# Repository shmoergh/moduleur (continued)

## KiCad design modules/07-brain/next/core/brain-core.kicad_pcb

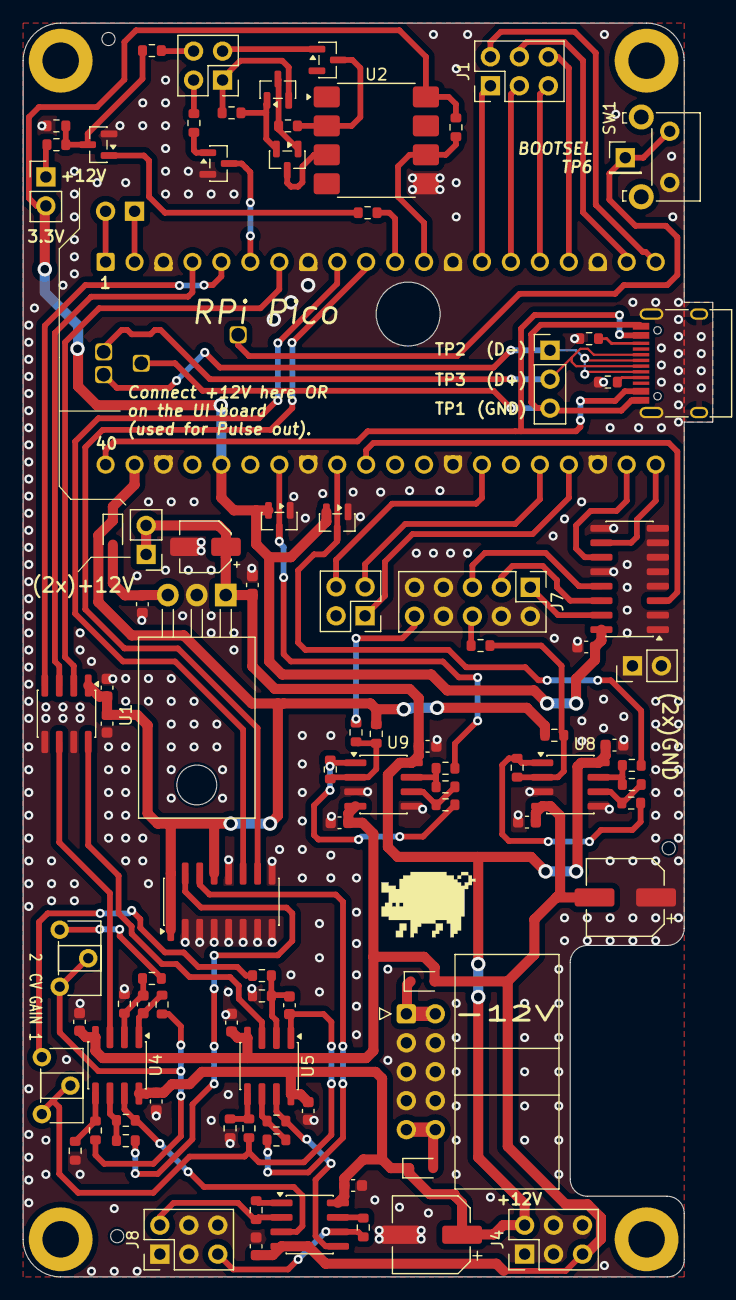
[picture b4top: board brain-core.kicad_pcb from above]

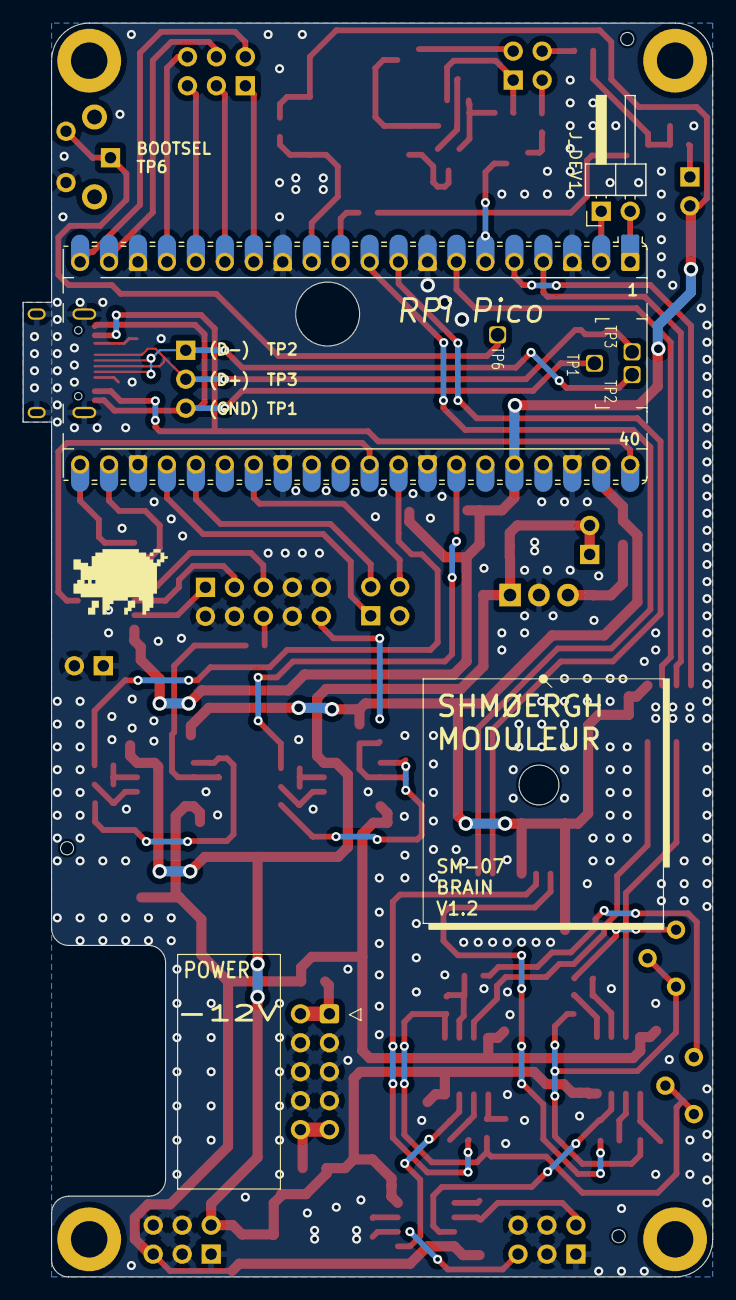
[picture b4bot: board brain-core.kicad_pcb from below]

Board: 2 copper layers, 60.5 x 110.0 mm, 99 parts (2 on the bottom side), 84 nets.

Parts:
C1: 10u; CP_Elec_4x5.4
C2: 330n; C_0603_1608Metric_Pad1.08x0.95mm_HandSolder
C3, C6, C7, C8, C9, C12, C13, C14, C15, C16, C17, C19, C20: 100n; C_0603_1608Metric
C4, C5: 100u; CP_Elec_6.3x7.7
C10, C11: 22p; C_0603_1608Metric
C18: 10u; C_0603_1608Metric
D1, D2, D3: 1N5817; D_SOD-323
D4: BAT54; SOT-23
D5, D6: BAT54S; SOT-23
H1, H2, H3, H4: MountingHole; MountingHole_3.2mm_M3_DIN965_Pad
J1, J4, J8: Conn_02x03_Odd_Even; PinHeader_2x03_P2.54mm_Vertical
J2, J3: Conn_02x02_Odd_Even; PinHeader_2x02_P2.54mm_Vertical
J5, J9, J10: Conn_01x02; PinHeader_1x02_P2.54mm_Vertical
J6: Conn_02x05_Odd_Even; IDC-Header_2x05_P2.54mm_Horizontal
J7: Conn_02x05_Odd_Even; PinHeader_2x05_P2.54mm_Vertical
J11: Conn_01x01; PinHeader_1x01_P2.54mm_Vertical
J13: Conn_01x03; PinHeader_1x03_P2.54mm_Vertical
J_DEV1: Conn_01x02; PinHeader_1x02_P2.54mm_Horizontal
J_USB_C_EXTENSION1: USB_C_Receptacle_USB2.0_16P; USB_C_Receptacle_HRO_TYPE-C-31-M-12
Q1, Q3, Q6, Q7: MMBT3904; SOT-23
R1, R14, R15, R16, R17, R18, R19, R20, R21, R24, R26, R30, R31, R32, R33: 100k; R_0603_1608Metric
R2, R7: 3.3k; R_0603_1608Metric
R3: 10k; R_0603_1608Metric
R4: 7.5k; R_0603_1608Metric
R5: 2.2k; R_0603_1608Metric
R6: 120; R_0603_1608Metric
R8, R9: 47k; R_0603_1608Metric
R10, R11: 62k; R_0603_1608Metric
R12, R13, R22, R23, R34, R35: 1k; R_0603_1608Metric
R25, R27: 120k; R_0603_1608Metric
R28, R29: 33k; R_0603_1608Metric
R36, R37: 5.1k; R_0603_1608Metric
RV_CV_GAIN1, RV_CV_GAIN2: 10k; Potentiometer_ACP_CA6-H2,5_Horizontal
SW1: SW_SPST; SW_Tactile_SKHH_Angled
U1: LM7805_TO220; TO-220-3_Horizontal_TabDown
U2: 6N137; SOP-8_6.605x9.655mm_P2.54mm
U3: Pico; RaspberryPi_Pico_Common_Unspecified
U4, U5, U8, U9, U11: TL072; SOIC-8_3.9x4.9mm_P1.27mm
U6: MCP4822; SOIC-8_3.9x4.9mm_P1.27mm
U7: 74HC4053B; SOIC-16_3.9x9.9mm_P1.27mm
U10: 74HC4051; SOIC-16_3.9x9.9mm_P1.27mm

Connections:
+3.3V: C16.1, D5.2 (K), D6.2 (K), J10.2, R7.2, U2.8 (VCC), U3.36 (3V3), U10.16 (VCC)
+5V: C17.1, C18.1, D1.1 (K), R24.1, R26.1, U3.39 (VSYS), U6.1 (Vdd), U7.1 (B1), U7.13 (A1), U7.16 (VDD)
+12V: C1.1, C2.1, C4.1, C6.1, C8.1, C12.1, C14.1, C19.1, D2.1 (K), J4.2, J9.1, J9.2, J10.1, R3.2, U1.1 (VI), U4.8 (V+), U5.8 (V+), U8.8 (V+), U9.8 (V+), U11.8 (V+)
-12V: C5.2, C7.2, C9.2, C13.2, C15.2, C20.2, D3.2 (A), J4.5, U4.4 (V-), U5.4 (V-), U8.4 (V-), U9.4 (V-), U11.4 (V-)
/GPIO_2: U3.4 (GPIO2), U6.3 (SCK)
/GPIO_3: U3.5 (GPIO3), U6.4 (SDI)
/GPIO_4: Q1.3 (C), U3.6 (GPIO4)
/GPIO_5: U3.7 (GPIO5), U6.2 (~CS)
/GPIO_6: U3.9 (GPIO6), U7.11 (S1)
/GPIO_7: U3.10 (GPIO7), U7.10 (S2)
/GPIO_8: R2.1, U3.11 (GPIO8)
/GPIO_9: R7.1, U2.6 (VO), U3.12 (GPIO9)
/GPIO_16: U3.22 (GPIO17), U10.11 (S0)
/GPIO_17: U3.21 (GPIO16), U10.10 (S1)
/GPIO_26: U3.31 (GPIO26_ADC0), U10.3 (A)
/GPIO_27: D5.3 (COM), R34.2, U3.32 (GPIO27_ADC1)
/GPIO_28: D6.3 (COM), R35.2, U3.34 (GPIO28_ADC2)
/MCU/TP1: J13.3, J_USB_C_EXTENSION1.A1 (GND), J_USB_C_EXTENSION1.A12 (GND), J_USB_C_EXTENSION1.B1 (GND), J_USB_C_EXTENSION1.B12 (GND), U3.44 (TP1)
/MCU/TP2: J13.1, J_USB_C_EXTENSION1.A7 (D-), J_USB_C_EXTENSION1.B7 (D-), U3.45 (TP2)
/MCU/TP3: J13.2, J_USB_C_EXTENSION1.A6 (D+), J_USB_C_EXTENSION1.B6 (D+), U3.46 (TP3)
/MCU/TP6: J11.1, SW1.1 (A), U3.47 (TP6)
/MCU/UART_RX: J_DEV1.1, U3.2 (GPIO1)
/MCU/UART_TX: J_DEV1.2, U3.1 (GPIO0)
AUDIO_CV_IN_1: J7.6, R25.1
AUDIO_CV_IN_2: J7.10, R27.1
AUDIO_CV_OUT_1: J8.5, R23.2, U11.6 (-)
AUDIO_CV_OUT_2: J8.2, R22.2, U11.2 (-)
BTN_1: J3.1, U3.24 (GPIO18)
BTN_2: J3.3, U3.25 (GPIO19)
BTN_LED_1: J3.4, U3.27 (GPIO21)
GND: C1.2, C2.2, C3.2, C4.2, C5.1, C6.2, C7.1, C8.2, C9.1, C12.2, C13.1, C14.2, C15.1, C16.2, C17.2, C18.2, C19.2, C20.1, D5.1 (A), D6.1 (A), J4.1, J4.3, J4.4, J4.6, J5.1, J5.2, J6.3, J6.4, J6.5, J6.6, J6.7, J6.8, J7.2, J7.4, J7.7, J7.8, J7.9, J8.1, J8.3, J8.4, J8.6, J_USB_C_EXTENSION1.S1 (SHIELD), Q1.2 (E), Q3.2 (E), R4.1, R8.1, R9.1, R16.1, R17.1, R36.2, R37.2, SW1.2 (B), U1.2 (GND), U2.5 (GND), U3.3 (GND), U3.8 (GND), U3.13 (GND), U3.18 (GND), U3.23 (GND), U3.28 (GND), U3.33 (AGND), U3.38 (GND), U6.5 (~LDAC), U6.7 (Vss), U7.2 (B0), U7.3 (C1), U7.4 (C), U7.5 (C0), U7.6 (INH), U7.7 (VEE), U7.8 (VSS), U7.9 (S3), U7.12 (A0), U8.3 (+), U8.5 (+), U9.3 (+), U9.5 (+), U10.1 (A4), U10.2 (A6), U10.4 (A7), U10.5 (A5), U10.6 (~E), U10.7 (VEE), U10.8 (GND), U10.9 (S2), U10.12 (A3)
LED_1: J1.1, U3.14 (GPIO10)
LED_2: J1.3, U3.15 (GPIO11)
LED_3: J1.5, U3.16 (GPIO12)
LED_4: J1.6, U3.17 (GPIO13)
LED_5: J1.4, U3.19 (GPIO14)
LED_6: J1.2, U3.20 (GPIO15)
MIDI_4R: D4.1 (A), J2.3
MIDI_5T: J2.1, Q6.2 (E), R6.1
unnamed: C10.2, R12.1, U4.1
unnamed: C11.2, R15.1, RV_CV_GAIN1.2, RV_CV_GAIN1.3, U5.1
unnamed: C3.1, D1.2 (A), U1.3 (VO)
unnamed: D2.2 (A), J6.9, J6.10
unnamed: D3.1 (K), J6.1, J6.2
unnamed: D4.3 (K), R5.2, U2.2 (A)
unnamed: J_USB_C_EXTENSION1.A5 (CC1), R36.1
unnamed: J_USB_C_EXTENSION1.B5 (CC2), R37.1
unnamed: Q1.1 (B), R1.2
unnamed: Q3.1 (B), R2.2
unnamed: Q3.3 (C), R3.1, R4.2, R13.1
unnamed: Q6.1 (B), Q7.2 (E), R6.2
unnamed: Q6.3 (C), Q7.1 (B), R5.1
unnamed: Q7.3 (C), U2.3 (C)
unnamed: R10.2, RV_CV_GAIN2.1
unnamed: R11.2, RV_CV_GAIN1.1
unnamed: R12.2, R14.1, RV_CV_GAIN2.2, RV_CV_GAIN2.3
unnamed: R22.1, U11.1
unnamed: R23.1, U11.7
unnamed: R28.2, R30.1, U8.1
unnamed: R29.2, R31.1, U9.1
unnamed: R32.2, R34.1, U8.7
unnamed: R33.2, R35.1, U9.7
unnamed: J_USB_C_EXTENSION1.A4 (VBUS), J_USB_C_EXTENSION1.A9 (VBUS), J_USB_C_EXTENSION1.B4 (VBUS), J_USB_C_EXTENSION1.B9 (VBUS), U3.40 (VBUS)
unnamed: U4.3 (+), U6.6 (VB)
unnamed: C10.1, R8.2, R10.1, U4.2 (-)
unnamed: R14.2, R16.2, U4.5 (+)
unnamed: R19.1, R20.1, U4.6 (-)
unnamed: U5.3 (+), U6.8 (VA)
unnamed: C11.1, R9.2, R11.1, U5.2 (-)
unnamed: R15.2, R17.2, U5.5 (+)
unnamed: R18.2, R21.1, U5.6 (-)
unnamed: R18.1, U7.14 (A)
unnamed: R19.2, U7.15 (B)
unnamed: R24.2, R25.2, R28.1, U8.2 (-)
unnamed: R30.2, R32.1, U8.6 (-)
unnamed: R26.2, R27.2, R29.1, U9.2 (-)
unnamed: R31.2, R33.1, U9.6 (-)
unnamed: R20.2, U4.7, U11.3 (+)
unnamed: R21.2, U5.7, U11.5 (+)
POT_1: J7.5, U10.13 (A0)
POT_2: J7.3, U10.14 (A1)
POT_3: J7.1, U10.15 (A2)
PULSE_IN: J2.2, R1.1
PULSE_OUT: J2.4, R13.2

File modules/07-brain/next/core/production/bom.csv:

Designator,Footprint,Quantity,Value,LCSC Part #
C1,CP_Elec_4x5.4,1,10u,C46550410
"C10, C11",0603,2,22p,C1653
"C12, C13, C14, C15, C16, C17, C19, C20, C3, C6, C7, C8, C9",0603,13,100n,C14663
C18,0603,1,10u,C19702
C2,0603,1,330n,C188679
"C4, C5",CP_Elec_6.3x7.7,2,100u,C2836442
"D1, D2, D3",D_SOD-323,3,1N5817,C5190152
D4,SOT-23,1,BAT54,C22466368
"D5, D6",SOT-23,2,BAT54S,C7420333
"J1, J4, J8",PinHeader_2x03_P2.54mm_Vertical,3,Conn_02x03_Odd_Even,
"J10, J5, J9",PinHeader_1x02_P2.54mm_Vertical,3,Conn_01x02,
J11,PinHeader_1x01_P2.54mm_Vertical,1,Conn_01x01,
J13,PinHeader_1x03_P2.54mm_Vertical,1,Conn_01x03,
"J2, J3",PinHeader_2x02_P2.54mm_Vertical,2,Conn_02x02_Odd_Even,
J6,IDC-Header_2x05_P2.54mm_Horizontal,1,Conn_02x05_Odd_Even,
J7,PinHeader_2x05_P2.54mm_Vertical,1,Conn_02x05_Odd_Even,
J_DEV1,PinHeader_1x02_P2.54mm_Horizontal,1,Conn_01x02,
J_USB_C_EXTENSION1,USB_C_Receptacle_HRO_TYPE-C-31-M-12,1,USB_C_Receptacle_USB2.0_16P,C165948
"Q1, Q3, Q6, Q7",SOT-23,4,MMBT3904,C20526
"R1, R14, R15, R16, R17, R18, R19, R20, R21, R24, R26, R30, R31, R32, R33",0603,15,100k,C25803
"R10, R11",0603,2,62k,C23221
"R12, R13, R22, R23, R34, R35",0603,6,1k,C21190
"R2, R7",0603,2,3.3k,C22978
"R25, R27",0603,2,120k,C25808
"R28, R29",0603,2,33k,C4216
R3,0603,1,10k,C25804
"R36, R37",0603,2,5.1k,C23186
R4,0603,1,7.5k,C23234
R5,0603,1,2.2k,C4190
R6,0603,1,120,C22787
"R8, R9",0603,2,47k,C25819
"RV_CV_GAIN1, RV_CV_GAIN2","Potentiometer_ACP_CA6-H2,5_Horizontal",2,10k,
SW1,SW_Tactile_SKHH_Angled,1,SW_SPST,
U1,TO-220-3_Horizontal_TabDown,1,LM7805_TO220,
U10,SOIC-16_3.9x9.9mm_P1.27mm,1,74HC4051,C9386
"U11, U4, U5, U8, U9",SOIC-8_3.9x4.9mm_P1.27mm,5,TL072,C6961
U2,SOP-8_6.605x9.655mm_P2.54mm,1,6N137,C92651
U3,RaspberryPi_Pico_Common_Unspecified,1,Pico,
U6,SOIC-8_3.9x4.9mm_P1.27mm,1,MCP4822,C623653
U7,SOIC-16_3.9x9.9mm_P1.27mm,1,74HC4053B,C5647

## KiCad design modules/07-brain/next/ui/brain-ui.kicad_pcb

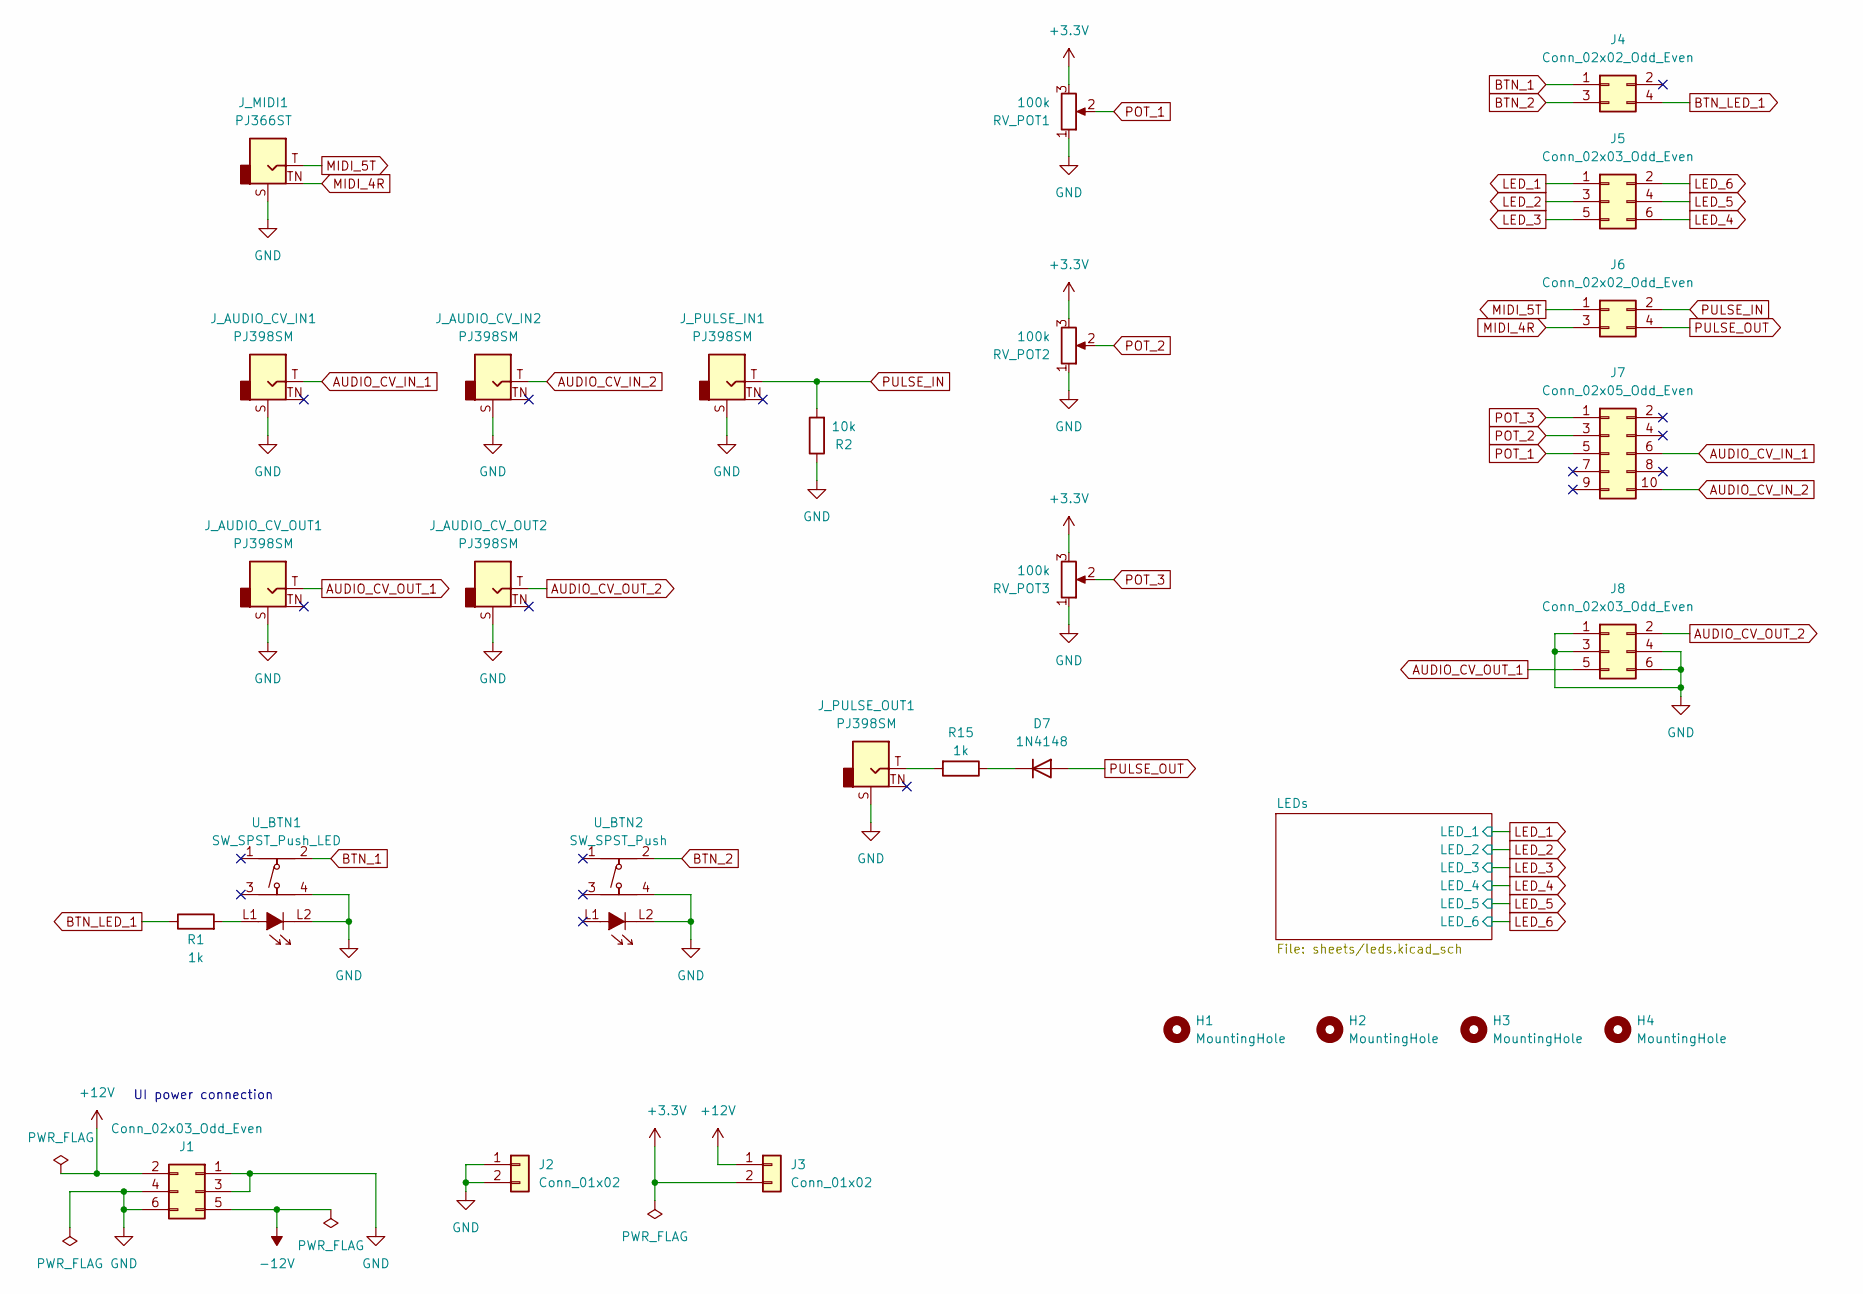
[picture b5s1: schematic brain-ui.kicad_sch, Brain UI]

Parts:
D7: 1N4148; D_DO-35_SOD27_P7.62mm_Horizontal
H1, H2, H3, H4: MountingHole; MountingHole_3.2mm_M3_DIN965_Pad
J1, J5, J8: Conn_02x03_Odd_Even; PinSocket_2x03_P2.54mm_Vertical; Part no. 200-SSW10301TD
J2, J3: Conn_01x02; PinSocket_1x02_P2.54mm_Vertical; Part no. 200-SSW10201TS
J4, J6: Conn_02x02_Odd_Even; PinSocket_2x02_P2.54mm_Vertical; Part no. 200-SSW10206TD
J7: Conn_02x05_Odd_Even; PinSocket_2x05_P2.54mm_Vertical; Part no. 200-SSW10501TD
J_AUDIO_CV_IN1, J_AUDIO_CV_IN2: PJ398SM; Jack_3.5mm_QingPu_WQP-PJ398SM_Vertical_CircularHoles; Part no. PJ398SM
J_AUDIO_CV_OUT1, J_AUDIO_CV_OUT2: PJ398SM; Jack_3.5mm_QingPu_WQP-PJ398SM_Vertical_CircularHoles; Part no. PJ398SM
J_MIDI1: PJ366ST; Jack_3.5mm_QingPu_WQP-PJ398SM_Vertical_CircularHoles; Part no. PJ366ST Stereo
J_PULSE_IN1: PJ398SM; Jack_3.5mm_QingPu_WQP-PJ398SM_Vertical_CircularHoles; Part no. PJ398SM
J_PULSE_OUT1: PJ398SM; Jack_3.5mm_QingPu_WQP-PJ398SM_Vertical_CircularHoles; Part no. PJ398SM
R1: 1k; R_Axial_DIN0207_L6.3mm_D2.5mm_P7.62mm_Horizontal; Part no. 603-MFR-25FRE52-1K
R2: 10k; R_Axial_DIN0207_L6.3mm_D2.5mm_P7.62mm_Horizontal; Part no. 603-MFR25SFTF52-10K
R15: 1k; R_Axial_DIN0207_L6.3mm_D2.5mm_P7.62mm_Horizontal; Part no. 603-MFR25SFTF52-10K
RV_POT1, RV_POT2, RV_POT3: 100k; Potentiometer_Bourns_Single-PTV09A; Part no. 652-PTV09A4025UB104
U_BTN1: SW_SPST_Push_LED; SPST_Circular_Pushbutton_LED; Part no. 611-D6RLRDF1LFS
U_BTN2: SW_SPST_Push; SPST_Circular_Pushbutton_LED; Part no. 611-D6R90F2LFS

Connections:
+3.3V: J3.2, RV_POT1.3, RV_POT2.3, RV_POT3.3
+12V: J1.2, J3.1; also elsewhere on the board
-12V: J1.5
AUDIO_CV_IN_1: J7.6, J_AUDIO_CV_IN1.T
AUDIO_CV_IN_2: J7.10, J_AUDIO_CV_IN2.T
AUDIO_CV_OUT_1: J8.5, J_AUDIO_CV_OUT1.T
AUDIO_CV_OUT_2: J8.2, J_AUDIO_CV_OUT2.T
BTN_1: J4.1, U_BTN1.2
BTN_2: J4.3, U_BTN2.2
BTN_LED_1: J4.4, R1.1
GND: H3.1, J1.1, J1.3, J1.4, J1.6, J2.1, J2.2, J8.1, J8.3, J8.4, J8.6, J_AUDIO_CV_IN1.S, J_AUDIO_CV_IN2.S, J_AUDIO_CV_OUT1.S, J_AUDIO_CV_OUT2.S, J_MIDI1.S, J_PULSE_IN1.S, J_PULSE_OUT1.S, R2.1, RV_POT1.1, RV_POT2.1, RV_POT3.1, U_BTN1.4, U_BTN1.L2, U_BTN2.4, U_BTN2.L2; also elsewhere on the board
LED_1: J5.1; also elsewhere on the board
LED_2: J5.3; also elsewhere on the board
LED_3: J5.5; also elsewhere on the board
LED_4: J5.6; also elsewhere on the board
LED_5: J5.4; also elsewhere on the board
LED_6: J5.2; also elsewhere on the board
MIDI_4R: J6.3, J_MIDI1.TN
MIDI_5T: J6.1, J_MIDI1.T
unnamed: D7.1 (K), R15.1
unnamed: J_PULSE_OUT1.T, R15.2
unnamed: R1.2, U_BTN1.L1
POT_1: J7.5, RV_POT1.2
POT_2: J7.3, RV_POT2.2
POT_3: J7.1, RV_POT3.2
PULSE_IN: J6.2, J_PULSE_IN1.T, R2.2
PULSE_OUT: D7.2 (A), J6.4

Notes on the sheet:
UI power connection

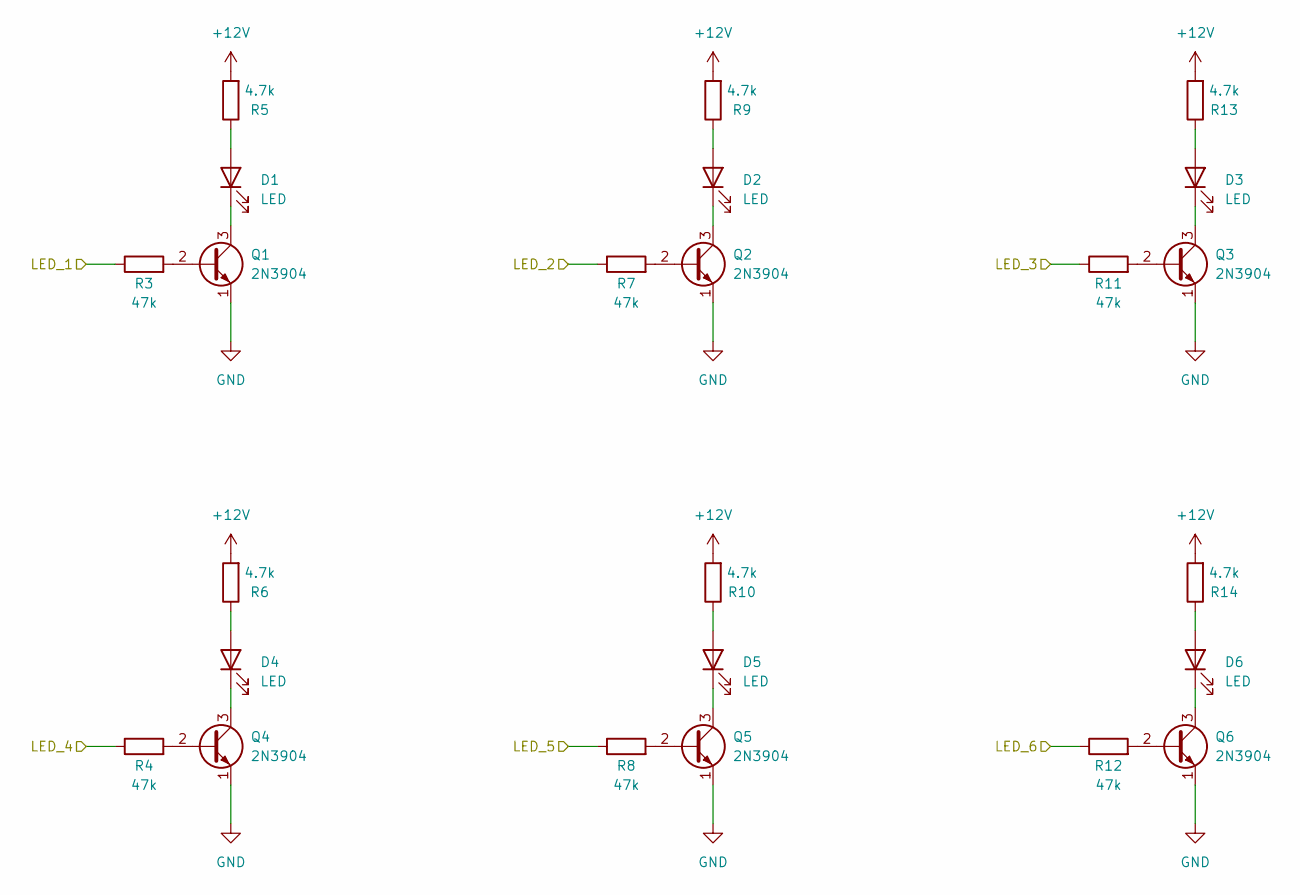
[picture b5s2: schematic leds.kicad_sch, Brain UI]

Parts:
D1, D2, D3, D4, D5, D6: LED; LED_D3.0mm
Q1, Q2, Q3, Q4, Q5, Q6: 2N3904; TO-92_Inline_Wide; Part no. 637-2N3904
R3, R4, R7, R8, R11, R12: 47k; R_Axial_DIN0207_L6.3mm_D2.5mm_P7.62mm_Horizontal; Part no. 603-MFR-25FRF52-47K; LCSC C25803
R5, R6, R9, R10, R13, R14: 4.7k; R_Axial_DIN0207_L6.3mm_D2.5mm_P7.62mm_Horizontal; Part no. 603-MFR25SFTF52-4K7

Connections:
+12V: R5.2, R6.2, R9.2, R10.2, R13.2, R14.2; also elsewhere on the board
GND: Q1.1 (E), Q2.1 (E), Q3.1 (E), Q4.1 (E), Q5.1 (E), Q6.1 (E); also elsewhere on the board
LED_1: R3.1; also elsewhere on the board
LED_2: R7.1; also elsewhere on the board
LED_3: R11.1; also elsewhere on the board
LED_4: R4.1; also elsewhere on the board
LED_5: R8.1; also elsewhere on the board
LED_6: R12.1; also elsewhere on the board
unnamed: D1.2 (A), R5.1
unnamed: D1.1 (K), Q1.3 (C)
unnamed: D2.2 (A), R9.1
unnamed: D2.1 (K), Q2.3 (C)
unnamed: D3.2 (A), R13.1
unnamed: D3.1 (K), Q3.3 (C)
unnamed: D4.2 (A), R6.1
unnamed: D4.1 (K), Q4.3 (C)
unnamed: D5.2 (A), R10.1
unnamed: D5.1 (K), Q5.3 (C)
unnamed: D6.2 (A), R14.1
unnamed: D6.1 (K), Q6.3 (C)
unnamed: Q1.2 (B), R3.2
unnamed: Q2.2 (B), R7.2
unnamed: Q3.2 (B), R11.2
unnamed: Q4.2 (B), R4.2
unnamed: Q5.2 (B), R8.2
unnamed: Q6.2 (B), R12.2

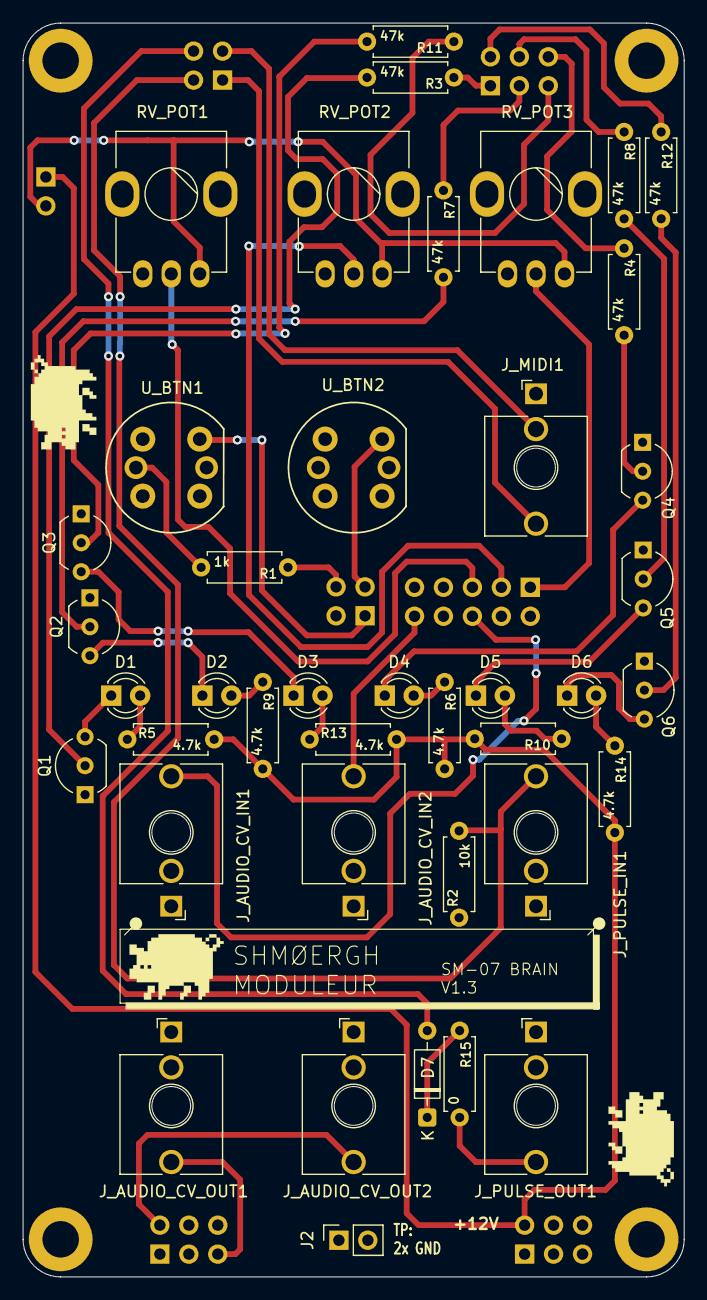
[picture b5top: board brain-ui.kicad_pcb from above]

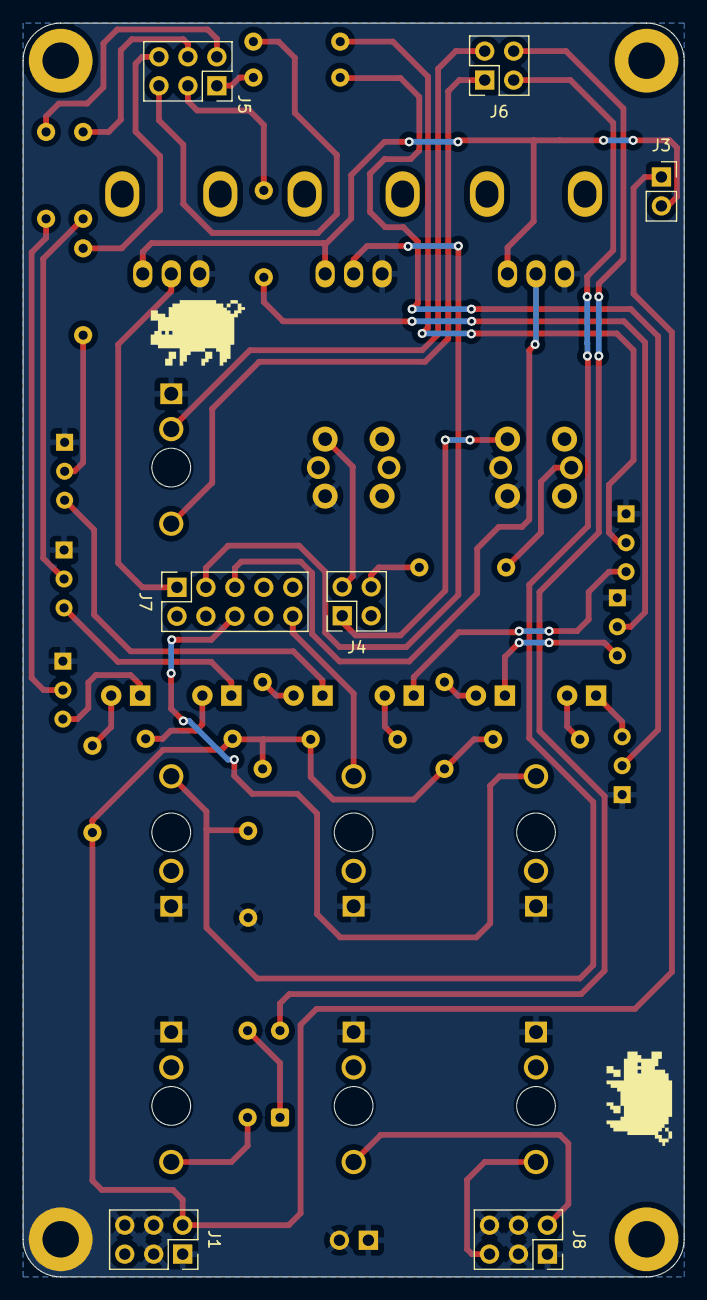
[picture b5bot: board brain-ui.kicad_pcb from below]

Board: 2 copper layers, 58.0 x 110.0 mm, 52 parts (7 on the bottom side), 44 nets.

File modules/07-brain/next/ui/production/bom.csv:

Designator,Footprint,Quantity,Value,LCSC Part #
"D1, D2, D3, D4, D5, D6",LED_D3.0mm,6,LED,
D7,D_DO-35_SOD27_P7.62mm_Horizontal,1,1N4148,
"J1, J5, J8",PinSocket_2x03_P2.54mm_Vertical,3,Conn_02x03_Odd_Even,
"J2, J3",PinSocket_1x02_P2.54mm_Vertical,2,Conn_01x02,
"J4, J6",PinSocket_2x02_P2.54mm_Vertical,2,Conn_02x02_Odd_Even,
J7,PinSocket_2x05_P2.54mm_Vertical,1,Conn_02x05_Odd_Even,
"J_AUDIO_CV_IN1, J_AUDIO_CV_IN2, J_AUDIO_CV_OUT1, J_AUDIO_CV_OUT2, J_PULSE_IN1, J_PULSE_OUT1",Jack_3.5mm_QingPu_WQP-PJ398SM_Vertical_CircularHoles,6,PJ398SM,
J_MIDI1,Jack_3.5mm_QingPu_WQP-PJ398SM_Vertical_CircularHoles,1,PJ366ST,
"Q1, Q2, Q3, Q4, Q5, Q6",TO-92_Inline_Wide,6,2N3904,
"R1, R15",R_Axial_DIN0207_L6.3mm_D2.5mm_P7.62mm_Horizontal,2,1k,
"R10, R13, R14, R5, R6, R9",R_Axial_DIN0207_L6.3mm_D2.5mm_P7.62mm_Horizontal,6,4.7k,
"R11, R12, R3, R4, R7, R8",R_Axial_DIN0207_L6.3mm_D2.5mm_P7.62mm_Horizontal,6,47k,C25803
R2,R_Axial_DIN0207_L6.3mm_D2.5mm_P7.62mm_Horizontal,1,10k,
"RV_POT1, RV_POT2, RV_POT3",Potentiometer_Bourns_Single-PTV09A,3,100k,
U_BTN1,SPST_Circular_Pushbutton_LED,1,SW_SPST_Push_LED,
U_BTN2,SPST_Circular_Pushbutton_LED,1,SW_SPST_Push,

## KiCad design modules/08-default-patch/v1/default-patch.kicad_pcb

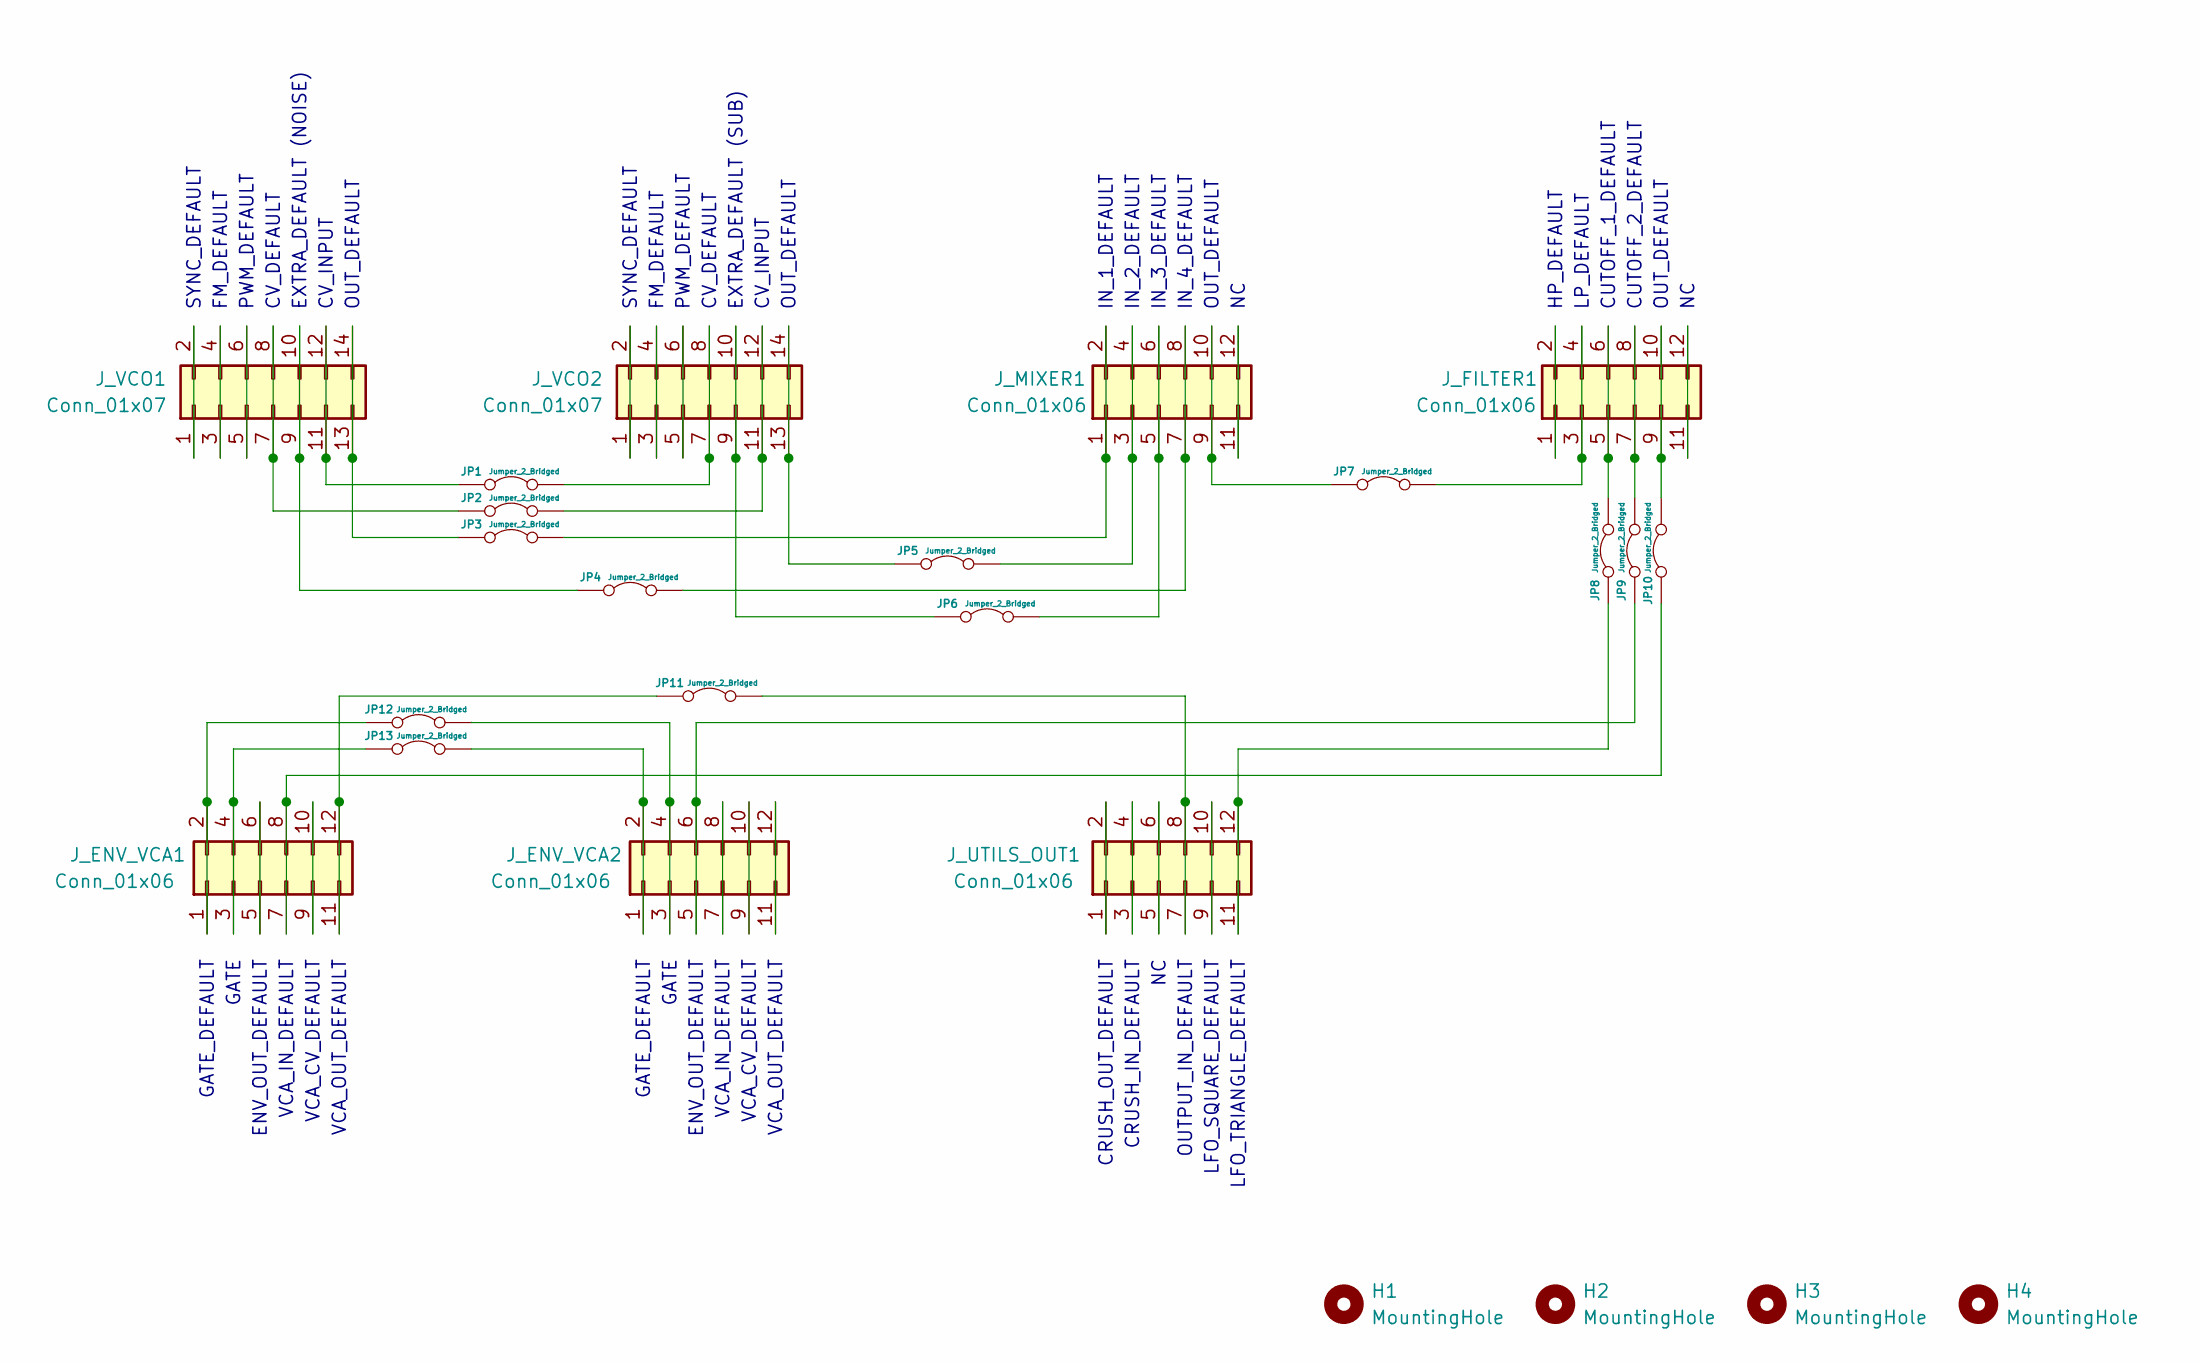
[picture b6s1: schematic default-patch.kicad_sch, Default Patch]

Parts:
H1, H2, H3, H4: MountingHole; MountingHole_3.2mm_M3
JP1, JP2, JP3, JP4, JP5, JP6, JP7, JP8, JP9, JP10, JP11, JP12, JP13: Jumper_2_Bridged; SolderJumper-2_P1.3mm_Bridged_RoundedPad1.0x1.5mm
J_ENV_VCA1, J_ENV_VCA2: Conn_01x06; PinHeader_2x06_P2.54mm_Vertical; Part No. 200-MTSW12009TS500
J_FILTER1: Conn_01x06; PinHeader_2x06_P2.54mm_Vertical; Part No. 200-MTSW12009TS500
J_MIXER1: Conn_01x06; PinHeader_2x06_P2.54mm_Vertical; Part No. 200-MTSW12009TS500
J_UTILS_OUT1: Conn_01x06; PinHeader_2x06_P2.54mm_Vertical; Part No. 200-MTSW12009TS500
J_VCO1, J_VCO2: Conn_01x07; PinHeader_2x07_P2.54mm_Vertical; Part No. 200-MTSW12009TS500

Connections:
unnamed: JP1.1 (A), J_VCO1.11, J_VCO1.12
unnamed: JP1.2 (B), J_VCO2.7, J_VCO2.8
unnamed: JP2.1 (A), J_VCO1.7, J_VCO1.8
unnamed: JP2.2 (B), J_VCO2.11, J_VCO2.12
unnamed: JP3.1 (A), J_VCO1.13, J_VCO1.14
unnamed: JP3.2 (B), J_MIXER1.1, J_MIXER1.2
unnamed: JP4.1 (A), J_VCO1.9, J_VCO1.10
unnamed: JP4.2 (B), J_MIXER1.7, J_MIXER1.8
unnamed: JP5.1 (A), J_VCO2.13, J_VCO2.14
unnamed: JP5.2 (B), J_MIXER1.3, J_MIXER1.4
unnamed: JP6.1 (A), J_VCO2.9, J_VCO2.10
unnamed: JP6.2 (B), J_MIXER1.5, J_MIXER1.6
unnamed: JP7.1 (A), J_MIXER1.9, J_MIXER1.10
unnamed: JP7.2 (B), J_FILTER1.3, J_FILTER1.4
unnamed: JP8.1 (A), J_UTILS_OUT1.11, J_UTILS_OUT1.12
unnamed: JP8.2 (B), J_FILTER1.5, J_FILTER1.6
unnamed: JP9.1 (A), J_ENV_VCA2.5, J_ENV_VCA2.6
unnamed: JP9.2 (B), J_FILTER1.7, J_FILTER1.8
unnamed: JP10.1 (A), J_ENV_VCA1.7, J_ENV_VCA1.8
unnamed: JP10.2 (B), J_FILTER1.9, J_FILTER1.10
unnamed: JP11.1 (A), J_ENV_VCA1.11, J_ENV_VCA1.12
unnamed: JP11.2 (B), J_UTILS_OUT1.7, J_UTILS_OUT1.8
unnamed: JP12.1 (A), J_ENV_VCA1.1, J_ENV_VCA1.2
unnamed: JP12.2 (B), J_ENV_VCA2.3, J_ENV_VCA2.4
unnamed: JP13.1 (A), J_ENV_VCA1.3, J_ENV_VCA1.4
unnamed: JP13.2 (B), J_ENV_VCA2.1, J_ENV_VCA2.2
unnamed: J_ENV_VCA1.5, J_ENV_VCA1.6
unnamed: J_ENV_VCA1.9, J_ENV_VCA1.10
unnamed: J_ENV_VCA2.7, J_ENV_VCA2.8
unnamed: J_ENV_VCA2.9, J_ENV_VCA2.10
unnamed: J_ENV_VCA2.11, J_ENV_VCA2.12
unnamed: J_FILTER1.1, J_FILTER1.2
unnamed: J_FILTER1.11, J_FILTER1.12
unnamed: J_MIXER1.11, J_MIXER1.12
unnamed: J_UTILS_OUT1.1, J_UTILS_OUT1.2
unnamed: J_UTILS_OUT1.3, J_UTILS_OUT1.4
unnamed: J_UTILS_OUT1.5, J_UTILS_OUT1.6
unnamed: J_UTILS_OUT1.9, J_UTILS_OUT1.10
unnamed: J_VCO1.1, J_VCO1.2
unnamed: J_VCO1.3, J_VCO1.4
unnamed: J_VCO1.5, J_VCO1.6
unnamed: J_VCO2.1, J_VCO2.2
unnamed: J_VCO2.3, J_VCO2.4
unnamed: J_VCO2.5, J_VCO2.6

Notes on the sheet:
HP_DEFAULT
VCA_IN_DEFAULT
GATE_DEFAULT
SYNC_DEFAULT
OUT_DEFAULT
FM_DEFAULT
PWM_DEFAULT
CV_DEFAULT
ENV_OUT_DEFAULT
VCA_CV_DEFAULT
IN_1_DEFAULT
VCA_OUT_DEFAULT
CRUSH_OUT_DEFAULT
OUTPUT_IN_DEFAULT
GATE
LP_DEFAULT
LFO_TRIANGLE_DEFAULT
IN_4_DEFAULT
CUTOFF_1_DEFAULT
IN_2_DEFAULT
CRUSH_IN_DEFAULT
IN_3_DEFAULT
CUTOFF_2_DEFAULT
EXTRA_DEFAULT (SUB)
CV_INPUT
EXTRA_DEFAULT (NOISE)
LFO_SQUARE_DEFAULT

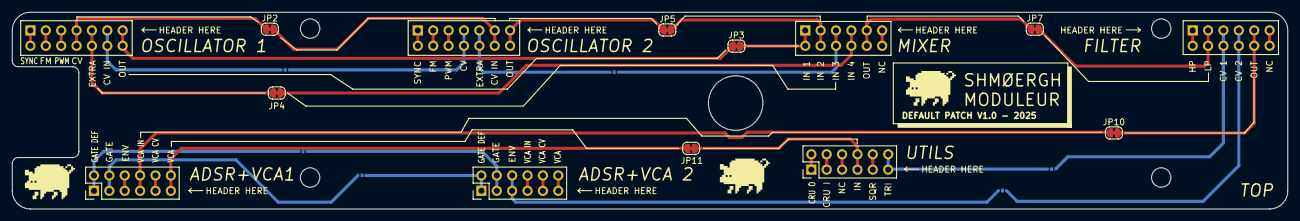
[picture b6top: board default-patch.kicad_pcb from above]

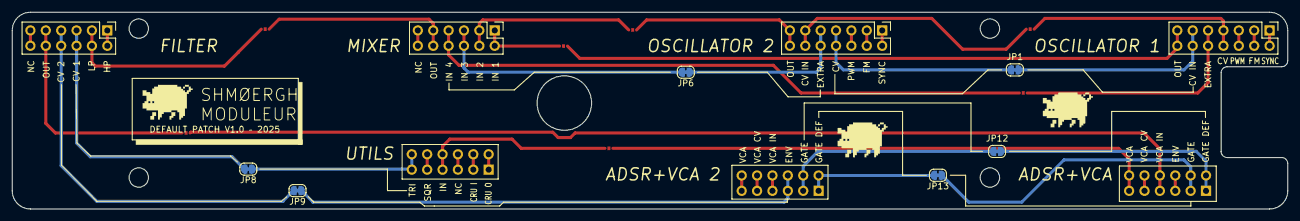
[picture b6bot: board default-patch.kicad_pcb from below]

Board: 2 copper layers, 210.7 x 32.5 mm, 24 parts (10 on the bottom side), 44 nets.
